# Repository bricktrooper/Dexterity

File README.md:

# Dexterity

Dexterity is a wearable gesture recognition device which uses custom hardware, firmware, and software to measure hand movement and finger position via an array of specialized sensors.  This data can be interpreted in real time to identify hand gestures and execute corresponding actions on a computer system.  Dexterity is designed to be a scalable and can be used as a peripheral for any electronic device.  This makes it suitable for a variety of applications involving gesture recognition.

A common approach towards gesture recognition is to use computer vision and machine learning in order to decipher gestures through a video feed.  This can be a computationally intensive task, depending on the complexity of the algorithms and the hardware capabilities, which in turn increases latency and decreases throughput.

Dexterity tackles this issue by placing sensors directly on a wearable glove.  The sensors are continuously sampled by an onboard microcontroller, which transmits the readings to a host PC via a high-speed serial UART connection.  The stronger hardware of the host can then be used to run interpretation algorithms on the raw readings.  This avoids placing unnecessary computational stress on a low power device while providing a more accurate model of the hand compared to computer vision.

## Hardware

Dexterity's hardware consists of a glove equipped with 8 sensors and a microcontroller.  Each finger has an attached flex sensor, which changes resistance when the finger bends.  This allows the position of each finger to be read accurately.  Additionally, a 3-axis analogue accelerometer is placed on the top of the glove, which can be used to determine the movement and orientation of the hand.

The device is powered by a custom circuit board with a Microchip PIC16F690 microcontroller.  This is an 8-bit low power computer that reads the flex sensors and accelerometer using its analogue-to-digital converter (ADC).

The board requires a wired serial connection, which doubles as the 5V power supply.  If a wireless serial transmitter is used in the future, then a separate battery will be needed to power the board.  The accelerometer is an ADXL335 3-axis sensor module, composed of analogue output pins for the X, Y, and Z spatial directions.  Resistors were added for the flex sensors to produce a voltage divider sampling node, and 0.1uF filtering capacitors were added for noise reduction.  The board also contains an enable/disable button and a status LED.  Typical current draw ranges between 3.5mA and 4mA with a 5V supply.

Autodesk EAGLE was used to complete schematic entry and board layout.  These files can be found under the `hardware` directory.

## Firmware

Custom firmware was developed to run on the PIC microcontroller.  This program runs forever as long as the board is powered.  The source code is located in the `firmware` directory.

The firmware reads the analogue voltages of each of the 8 sensors.  Each sensor is attached to an input pin, and the PIC will perform an ADC conversion on each of these analogue voltage inputs.  The microcontroller can also scale the readings between a certain range, which is useful for gesture interpretation.  If this is disabled, then the raw 10-bit ADC conversion values are returned instead.

The PIC transmits readings to a host device over a serial UART running at a baud rate of 115200 bits per second.  This results in less than 1ms of latency for data retrieval from the device.  The clock frequency of the PIC was increased to a maximum of 8MHz, which further reduces latency and increases the computational power.

The PIC can also send the current calibration settings to the host.  Similarly, the host can upload new calibration settings to the PIC.  Additionally, the host can tell the device to enable or disable scaling of the sensor readings.

The host and the device communicate using a set of short string messages.  The host will send messages to the PIC, and the firmware will continuously poll for a message.  If a valid message is received, the PIC will perform the requested action and return an ACK message signalling a success or an error.  In some cases, a data payload is sent instead of an ACK, such as a set of sensor readings.

## Software

The software is responsible for communicating with the device and interpreting the sensor readings to execute a specific function on the host computer.  The source code is located in the `software` directory of the repository.

The device must be connected to the computer via a serial-to-USB cable.  It is important that this cable is a **5V** variant and not a 3.3V variant, as a 5V supply is needed to power the device hardware.  The cable must have an embedded **FTDI FT232RL** chip, which allows the serial UART to appear as a USB device.  FTDI drivers may need to be installed to have this cable function correctly.

The software opens a serial port file descriptor and sets the attributes to match the settings used by the PIC.  The user can issue a variety of commands via the `dexterity` command line utility that the software compiles to.  While the main software is running, the program will continuously request sensor readings from the PIC.  Once the data arrives, it will be fed to an interpretation algorithm, which attempts to identify a hand gesture based on the average error and the tolerance.

If the readings match one of the valid gestures from the gesture list, then a corresponding action will be performed on the computer.  This might include playing/pausing a song, or moving and clicking the mouse.  There are different control modes as well, each with a different set of gestures.  The modes can be cycled through by flicking the thumb down and up again while keeping the other fingers straight and relaxed.  Pressing the push button on the board at any point will suspend the program.  The program can be resumed by pressing the button again.

The program will require a calibration file and a gestures file in order to function.  These can be found under the `config` directory, and can be easily modified for the application.

**NOTE:** The current software only works on Mac OS X, since it makes use of Apple's Quartz Event Services API.  This allows the program to inject events into HID stream in order to emulate mouse and keyboard events.  The software only supports the device as a computer peripheral, but the generality of the design can allow the user to control any electromechanical function by binding the trigger software appropriately.

## Compilation Instructions

### Build System

Dexterity uses a Makefile build system that compiles each source file separately and links the object files together at the end to produce a program binary.  The build system uses the `gcc` compiler to automatically generate file dependencies based on included header files.  These dependencies are stored in `*.d` dependency files.  The Makefiles use generalized pattern rules, which makes them highly scalable.  This allows additional source files to be added without major modifications to the Makefile.  All artifacts of the build system are placed in `bin` directories under the `software` and `firmware` source code folders.

### Firmware

The firmware is written in a dialect of C that is specific to the PIC microcontroller. The source code must be compiled using Microchip's XC8 compiler toolchain.  You will need to have these tools installed in order to build the firmware.  To compile the code, navigate to the `firmware` directory of the repository and execute the Makefile by typing `make`.  This will compile the code using the `xc8-cc` compiler and linker.  Each source file is compiled separately into object files with the `*.p1` extension, which are then linked into a single `*.hex` binary file and stored in the `bin` folder.  If you would like to view the PIC memory usage statistics, then add `MEMORY=show` as an argument when running `make`.  The firmware also has an alternate test program, which runs simple tests for each part of the firmware.  You can compile this version using the `test` target and by adding `TYPE=<TEST_NAME>`, where `TEST_NAME` can be any of the following:
* `INIT_TEST`
* `UART_TEST`
* `ADC_TEST`
* `ACCEL_TEST`
* `FLEX_TEST`
* `LED_TEST`
* `BUTTON_TEST`

To compile the test program:
```
make test TYPE=<TEST_NAME>
```
The test program can only be compiled from within the `firmware` directory.

### Software

The software is implemented in C with a few special functions written in Objective-C
The source code must be compiled using the Apple's version of the LLVM Clang compiler, which is able to link to the frameworks required for emulating the mouse and keyboard on Mac OS X.  Note that this will require installation of Apple's XCode command line tools, which include Clang and the Apple frameworks.  To compile the code, navigate to the `software` directory of the repository and execute the Makefile by typing `make`.  This will compile the code using the `clang` compiler and linker.  Each source file is compiled separately into object files with the `*.o` extension, which are then linked into an executable binary file and stored in the `bin` folder.  This `dexterity` binary file is executable from the command line.

### Top Level Build

Both the software and the firmware can be compiled at the same time by executing `make` from the top-level directory.  The top level Makefile will invoke the Makefiles from the `software` and `firmware` directories and place all generated artifacts in their respective `bin` folders, while also copying the binaries to a top level `artifacts` folder.

## Loading the Firmware

**IMPORTANT:** Before loading the firmware, slide the switch on the circuit board **away from the PIC** and **towards the edge of the board**.  This will disconnect the VREF input pin from the 3.3V pin on the ADXL335, putting the line in a high impedance state and eliminating any signalling conflicts.  Failing to do this will prevent the PICKit3 from interfacing with the PIC.

The firmware should be loaded onto the device using a PICKit3 serial in-circuit programmer.  Microchip's MPLAB IPE is required to connect to the PIC and load the `*.hex` firmware binary.

## Running the Program

**IMPORTANT:** Before running the program, ensure that the slide switch on the circuit board is moved **towards the PIC** and **away from the edge of the board**.  This attaches the VREF input of the PIC to the 3.3V pin on the ADXL335.  Failing to do this will result in the device producing an incorrect ADC reading for the acceleration axes.

The `dexterity` binary produced by compiling the software is an executable file.  You can run this from the command line:
```
./dexterity
```

This should bring up a list of available subcommands.  If you would like to use this command from anywhere, add the location of the binary to your PATH variable.

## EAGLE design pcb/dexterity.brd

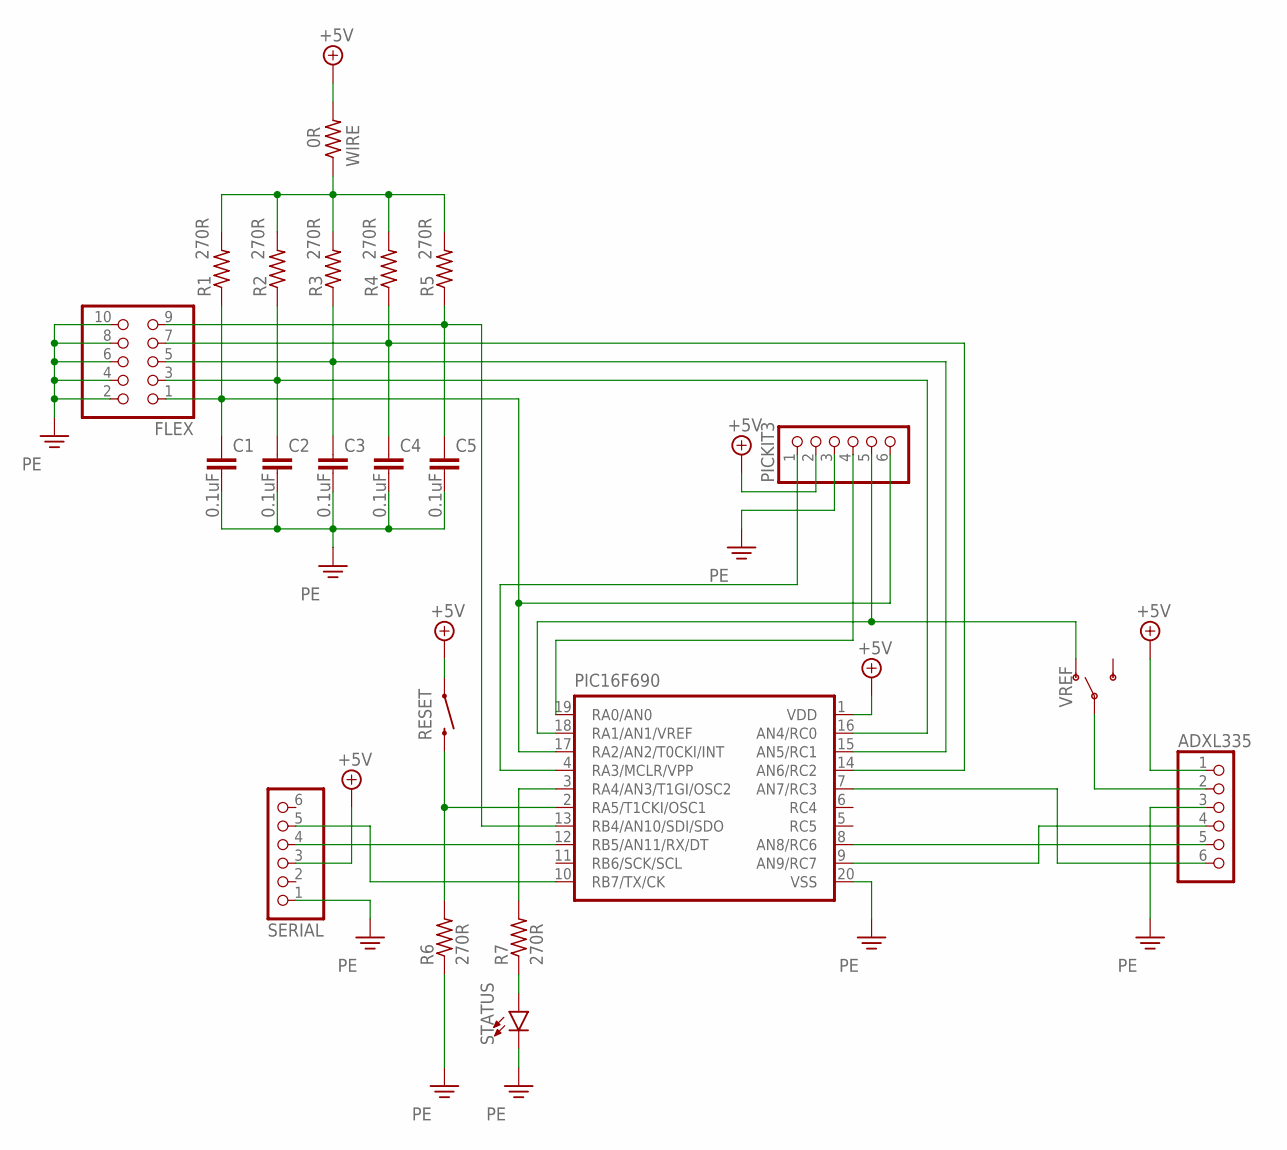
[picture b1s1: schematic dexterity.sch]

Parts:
ADXL335: PINHD-1X6/90; 1X06/90
C1, C2, C3, C4, C5: 0.1uF; C050-025X075
FLEX: PINHD-2X5/90; 2X05/90
PIC16F690: PIC16F6XX; DIL20
PICKIT3: PINHD-1X6; 1X06
R1, R2, R3, R4, R5, R6, R7: 270R; 0207/7
RESET: MOMENTARY-SWITCH-SPST-PTH-6.0MM; TACTILE_SWITCH_PTH_6.0MM
SERIAL: PINHD-1X6/90; 1X06/90
STATUS: LED3MM; LED_3MM
VREF: SWITCH-SPDT-PTH-11.6X4.0MM; SWITCH_SPDT_PTH_11.6X4.0MM
WIRE: 0R; 0207/7

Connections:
+5V: ADXL335.1, PIC16F690.1 (VDD), PICKIT3.2, R1.2, R2.2, R3.2, R4.2, R5.2, RESET.1, SERIAL.3, WIRE.1, WIRE.2
GND: ADXL335.3, C1.2, C2.2, C3.2, C4.2, C5.2, FLEX.2, FLEX.4, FLEX.6, FLEX.8, FLEX.10, PIC16F690.20 (VSS), PICKIT3.3, R6.1, SERIAL.1, STATUS.K (C)
unnamed: ADXL335.2, VREF.2
unnamed: PIC16F690.18 (RA1/AN1/VREF), PICKIT3.5, VREF.1 (O)
unnamed: PIC16F690.12 (RB5/AN11/RX/DT), SERIAL.4
unnamed: PIC16F690.10 (RB7/TX/CK), SERIAL.5
unnamed: PIC16F690.3 (RA4/AN3/T1GI/OSC2), R7.2
unnamed: ADXL335.5, PIC16F690.8 (AN8/RC6)
unnamed: ADXL335.6, PIC16F690.7 (AN7/RC3)
unnamed: PIC16F690.4 (RA3/MCLR/VPP), PICKIT3.1
unnamed: C2.1, FLEX.3, PIC16F690.16 (AN4/RC0), R2.1
unnamed: PIC16F690.19 (RA0/AN0), PICKIT3.4
unnamed: C1.1, FLEX.1, PIC16F690.17 (RA2/AN2/T0CKI/INT), PICKIT3.6, R1.1
unnamed: C3.1, FLEX.5, PIC16F690.15 (AN5/RC1), R3.1
unnamed: C4.1, FLEX.7, PIC16F690.14 (AN6/RC2), R4.1
unnamed: C5.1, FLEX.9, PIC16F690.13 (RB4/AN10/SDI/SDO), R5.1
unnamed: ADXL335.4, PIC16F690.9 (AN9/RC7)
unnamed: R7.1, STATUS.A
unnamed: PIC16F690.2 (RA5/T1CKI/OSC1), R6.2, RESET.3 (2)

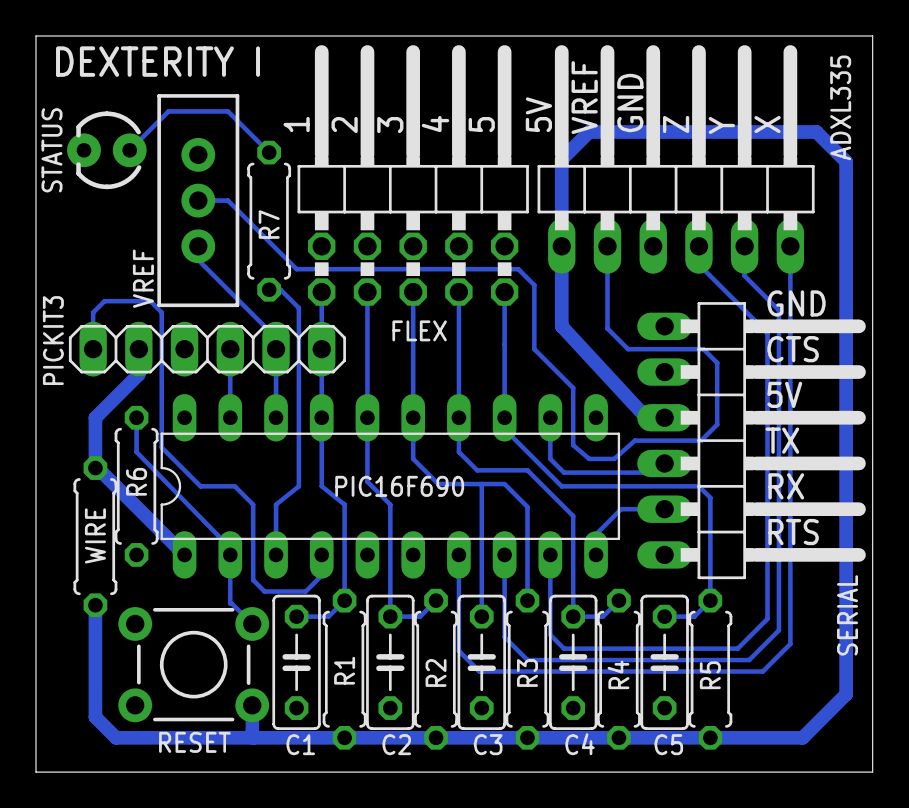
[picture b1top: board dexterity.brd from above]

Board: 2 copper layers, 46.5 x 40.9 mm, 21 parts (0 on the bottom side), 19 nets.

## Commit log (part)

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2020-02-05 init: Add basic init code for PIC16F690
    Basic initialization code for
    PIC operation. Configures the
    following features of the device:
    - Digital I/O
    - Analogue I/O
    - Internal Oscillator 4MHz (~3.6864MHz)
2020-02-05 uart: Add basic init code for testing
    This is later replaced by the init module
2020-02-05 uart: Implement UART send function to output data serially
    This can be used to output to a console that
    operates at the same baud rate (9600).
2020-02-05 uart: Tweak Makefile printing
2020-02-05 uart: update init.h path.
    init.h is now in the init module.
2020-02-05 uart: Update test.c with new TX function name
    Also changed 'OK' return code to 'SUCCESS'.
2020-02-06 uart: Simplify Makefile object list
    Introduced a new variable 'ART', which
    is a list of objects prefixed with the
    the artifact directory (out).
2020-02-13 Keep out directories during make clean
    Only delete the artifacts within the
    out directories. This simplifies and
    speeds up the Makefiles.
2020-02-13 main: Add top-level Makefile
    Can be used to build and clean
    individual modules and their
    test code.
2020-02-20 uart: Transmit and receive data by byte
    Added functions that transmit and receive
    data one byte at a time. The functions for
    sending and receiving buffers of data were
    re-implemented using these functions.
2020-02-20 serial: Use NEWLINE more often to improve readability
2020-02-20 adc: Create ADC Makefile and build directory
2020-02-23 Rename module test files as '<module>-test.c'
    Originally 'test.c' was being used for all
    modules, but this was causing cross-module
    dependency confusion.
2020-08-19 pcb: Create first version of PCB
    Board was designed in EAGLE based on a schematic of the breadboard
    layout. The board will have the following features:
    - status LED
    - flex sensor angled DIP
    - accelerometer angled SIP
    - UART serial angled SIP
2020-08-20 flex: Read flex sensors using ADC
    The flex sensor values were scaled to the 0 <-> 100 range.
    This should be further calibrated when the flex sensors are on the
    glove. The addition of filtering capacitors will also change the
    calibration settings.
2020-10-16 firmware: Add basic init code for testing
    This is later replaced by the init module
2020-10-16 firmware: Successfully transfer one character
    The settings are Fosc = 4MHz,
    BRGH = 1, and SPBRG = 23.
2020-10-16 build: Tweak Makefile printing
2020-10-16 build: Update Makefile to use init module
    the UART test.c should use the init module
    instead of the old local init code.
2020-10-16 firmware: Update test.c with new TX function name
    Also changed 'OK' return code to 'SUCCESS'.
2020-10-16 build: Suppress memory summary
2020-10-16 firmware: Move all firmware source files to same directory
    This will simplify the build system and eliminate the need for complex
    recursive Makefiles.
2020-10-16 software: Add special logging functions
    These are used to organize program output messages.
2020-10-16 firmware: Tweak rule name for making all tests
2020-10-16 firmware: Add simple message recognition
    The PIC will accept simple messages and print a result to the UART.
    The message must be terminated by a carriage return [ENTER] keypress.
2020-10-16 firmware: Fix pin assignments
2020-10-16 build: Rewrite build system as generic Makefiles
    The Makefiles are now identical and generic
    across all modules. Additional 'config.mk'
    files have been added where the build settings
    and dependencies can be specified for each module.
2020-10-16 build: Create ADC Makefile and build directory
2020-10-16 firmware: Sample all sensors and print readings to UART
2020-10-16 common: Add strings for accel and flex in common
    This is just for printing aesthetics.
2020-10-16 firmware: Create pins.h containing pinout constants
    This file is used to store macros that are aliased with the pin names
    and analogue channels for the various peripherals on the board. This
    includes the accelerometer, flex sensors, LED, and button.
2020-10-16 software: Clean up serial code
    Added checks for invalid serial port FD.
2020-10-16 software: Rename messages module to 'logs'
    Log levels will be added later. This will be used to suppress unwanted
    log messages.
2020-10-16 software: Develop serial I/O module
    This code will be used to manage the UNIX serial port.
    It is capable of reading and writing data to and from the device.
    Note that the transmission has delays inserted between each byte,
    which avoids overrunning the PIC's RX buffer.
2020-10-16 firmware: Ignore ADC build artifacts directory
2020-10-16 firmware: Combine all firmware tests into one file
    Each test is a separate function.
    There is no need for dedicated test files.
2020-10-16 firmware: Fix TRISB comment
    RB4 was marked as N/C.
2020-10-16 common: Change max message size macro name
2020-10-16 firmware: Use NEWLINE more often to improve readability
2020-10-16 build: Fix Makefile double link
    The Makefile was linking two copies of dexterity.o
2020-10-16 software: Flush serial RX buffer before R/W cycle
    The serial input buffer should be flushed of any data remnants before
    the next R/W cycle takes place. This will prevent old data from being
    consumed along with the new data.
2020-10-16 firmware: Add test code for Serial O/I
    Currently only tests printing over UART.
2020-10-16 software: Remove redefinition of return code macros
    These are already in the universal header.
2020-10-16 common: Move important definitions to universal header
    The dexterity.h header will contain struct definitions and macros
    that should be consistent across the firmware and the software.
    Add symbolic link to universal header for the software source code.
    Make sure to set 'core.symlinks' appropriately using 'git config'.
    This will allow Git to properly interpret the symlink.
2020-10-16 software: Improve file read/write
    The read file function will now load the entire file into a buffer.
2020-10-16 software: Export and import calibration from a file
    The calibration settings can be loaded from a file or saved to a file.
    The file is easy to read and can be modified by hand if required.
    Also applied scaling when calibrating the zero point. This required
    the exposure of the scaling function in common.
2020-10-16 common: Rename some types to make more sense
2020-10-16 build: Prevent Makefile from regenerating dependencies during a clean
    We don't need to generate dependencies when running 'make clean'
2020-10-16 firmware: Use a switch statement for message handling
    Since there are many messages, a switch statement may be more
    efficient than cascading if-else statements, as the compiler
    may use a lookup table.
2020-10-16 software: Use enum in for loop
2020-10-16 build: Fix individual target recipes
    The artifacts should be copied to the top level even when individual
    recipes are run. Also fixed the printing to work with the -j option.
2020-10-17 build: Add Makefile command line arg to show PIC memory summary
    The memory summary is off by default but can be show by inserting
    'MEMORY=show' as a command line argument of make.
2020-10-18 software: Fix some minor Clang warnings
2020-10-19 software: Move mouse relative to current position
2020-10-20 software: Support mouse dragging
2020-10-24 firmware: Increase PIC internal oscillator frequency to 8MHz
    This effectively doubles the device operation speed from the original
    4MHz frequency, resulting in faster computation and sampling of sensors.
    This will also result in increased thermals for the chip.
2020-10-24 software: Prevent cursor from moving beyond the screen limits
    Quartz already prevents this but the mouse coordinates can still become
    invalid. Currently this uses the hardcoded limits of a 1920x1080 screen
    but these should be set dynamically at runtime.
2020-10-27 software: Convert indentation to tabs in mouse.c
2020-10-28 common: Reorganize calibration structs to enable custom scaling ranges
    The scaling range can now be set using a calibration file.
2020-10-29 software: Change sample colours and formatting
2020-10-31 common: Restructure calibration struct to use 2D array
    This allows us to iterate over the analogue calibration parameters
    easily, similar to how the acceleration and flex sensor readings can
    be iterated over using their enums.
2020-10-31 software: Change sample command to update on the same line
    This is better than spamming the terminal with sample lines.
2020-11-02 software: Check for success when writing to calibration file
2020-11-02 software: Fix segfault in phase label mismatch printing
2020-11-03 software: Add format specifier checking for log_print and fix warnings
2020-11-03 software: Remove unnecessary parentheses for address operator
2020-11-08 software: Refactor gesture comparison functions
    gesture_compare() will auto-increment the phase if there is a match.
    It will return true when the last phase is reached.
2020-11-09 software: Start the program in the disabled state
2020-11-26 software: Trace file name, line number, and function name in logs
    This can be disabled with log_trace().
2020-11-28 software: Left click fast for double click
2020-11-28 software: Add gesture for showing all windows
2020-12-02 software: Control volume using gestures
    Volume is a separate mode of operation. If all the hand fingers are
    clasped, then the volume can be controlled by tiling left and right.
    Also improved the gesture for overview so that it does not get mistaken
    with a recovery from a drag gesture.
2020-12-03 software: Free gestures via end() function
    This allows the gestures to be freed via a signal handler as well as
    normally if there is no interrupt.
2020-12-03 common: Change WARNING return code from 1 to -2
    A UNIX signals might have a value of 1 and this should not be confused
    with an return code of WARNING. All three return codes (ERROR, SUCCESS,
    and WARNING) will be <= 0 to avoid conflicting with UNIX signal values
    which are > 0 (these signals may interrupt the program via end()).
2020-12-05 software: Header whitespace formatting
2020-12-06 build: Don't rename top-level artifacts
2020-12-12 software: Overwrite control printing
    This prevents the program from continuously
    dumping output to the terminal.
2020-12-18 software: Display help even when device is unplugged
    the init() function should only run for commands that require it.
    This does not include help messages. Also improved the signal
    handler and cleanup functions.
2021-07-08 software: Comments and spelling

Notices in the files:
parts and their libraries:
SparkFun-Switches: Licensing: Creative Commons ShareAlike 4.0 International - https://creativecommons.org/licenses/by-sa/4.0
